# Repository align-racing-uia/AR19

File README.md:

<h1 align="center"> Align Racing 2019 </h1> <br>
<p align="center">
    
</p>

<!-- START doctoc generate TOC please keep comment here to allow auto update -->
<!-- DON'T EDIT THIS SECTION, INSTEAD RE-RUN doctoc TO UPDATE -->
## Table of contents

- [Introduction](#introduction)
- [Align Racing UiA](#alignracinguia)
- [Rules for file structure](#rulesforfilestructure)
- [License](#license)

<!-- END doctoc generated TOC please keep comment here to allow auto update -->

## Introduction

This is the repository for Align Racing's 2019 formula student race car.

## Align Racing UiA

<a href="http://www.alignracing.no/">Align Racing UiA (AR)</a> is a multidisciplinary student organisation at <a href="https://www.uia.no/">The University of Agder (UiA)</a>, that take part in the world’s largest yearly engineering competition; <a href="https://www.imeche.org/events/formula-student">Formula Student (FS)</a>. The organisation continuously consists of around 60 students, from a wide variety of disciplines. The competition includes developing, building, budgeting and marketing a small scale formula type racing car. AR takes this a bit further by having more focus on developing a strong organisation, open for all disciplines, that gives the members a taste of future work-life.

## Rules for directory structure
<h4>General directory structure:</h4>

* AR”YEAR”
    * AR”YEAR”_“PROJECT”
        - AR”YEAR”_“PROJECT”
            - “PROJECT”_code
            - “PROJECT”_datasheets
            - “PROJECT”_images
            - “PROJECT”_schematic
            - “PROJECT”_simulink

<h4>Directory structure example:</h4>

* AR19
    * AR19_ETC
        - AR19_ETC_ACM_ETB
            - ACM_ETB_code
            - ACM_ETB_datasheets
            - ACM_ETB_images
            - ACM_ETB_schematic
            - ACM_ETB_simulink

## License
All content included in this Git repository is under the license:

Creative Commons Attribution-NonCommercial-ShareAlike 4.0 International

You are free to:
* <b> Share </b> — copy and redistribute the material in any medium or format
* <b> Adapt </b> — remix, transform, and build upon the material

Under the following terms:
* <b> Attribution </b> — You must give appropriate credit, provide a link to the license, and indicate if changes were made. You may do so in any reasonable manner, but not in any way that suggests the licensor endorses you or your use.
* <b> NonCommercial </b> — You may not use the material for commercial purposes.
* <b> ShareAlike </b> — If you remix, transform, or build upon the material, you must distribute your contributions under the same license as the original.
* <b> No additional restrictions </b> — You may not apply legal terms or technological measures that legally restrict others from doing anything the license permits.

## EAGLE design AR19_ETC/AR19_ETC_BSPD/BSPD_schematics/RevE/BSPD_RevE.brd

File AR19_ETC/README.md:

<h1 align="center"> Align Racing 2019 Electronic Throttle Control </h1> <br>
<p align="center">
    
</p>

<!-- START doctoc generate TOC please keep comment here to allow auto update -->
<!-- DON'T EDIT THIS SECTION, INSTEAD RE-RUN doctoc TO UPDATE -->
## Table of contents

- [Introduction](#introduction)
- [Align Racing UiA](#alignracinguia)
- [Contributors](#contributors)
- [Acknowledgments](#acknowledgments)
- [License](#license)

<!-- END doctoc generated TOC please keep comment here to allow auto update -->

## Introduction

This is the directory for Align Racing 2019 Electronic Throttle Control bachelor thesis. The goal of the project is to develop and implement an electronic throttle control system for a Formula Student race car.

## Align Racing UiA

<a href="http://www.alignracing.no/">Align Racing UiA (AR)</a> is a multidisciplinary student organisation at <a href="https://www.uia.no/">The University of Agder (UiA)</a>, that take part in the world’s largest yearly engineering competition; <a href="https://www.imeche.org/events/formula-student">Formula Student (FS)</a>. The organisation continuously consists of around 60 students, from a wide variety of disciplines. The competition includes developing, building, budgeting and marketing a small scale formula type racing car. AR takes this a bit further by having more focus on developing a strong organisation, open for all disciplines, that gives the members a taste of future work-life.

## Contributors

<div align="center">

</div>

<div align="center">

</div>

## Acknowledgments

Special thanks to our supervisor <a href="https://www.uia.no/kk/profil/kristimk">Kristian Muri Knausgård</a> for helping and supporting our project.

## License
All content included in this Git repository is under the license:

Creative Commons Attribution-NonCommercial-ShareAlike 4.0 International

You are free to:
* <b> Share </b> — copy and redistribute the material in any medium or format
* <b> Adapt </b> — remix, transform, and build upon the material

Under the following terms:
* <b> Attribution </b> — You must give appropriate credit, provide a link to the license, and indicate if changes were made. You may do so in any reasonable manner, but not in any way that suggests the licensor endorses you or your use.
* <b> NonCommercial </b> — You may not use the material for commercial purposes.
* <b> ShareAlike </b> — If you remix, transform, or build upon the material, you must distribute your contributions under the same license as the original.
* <b> No additional restrictions </b> — You may not apply legal terms or technological measures that legally restrict others from doing anything the license permits.

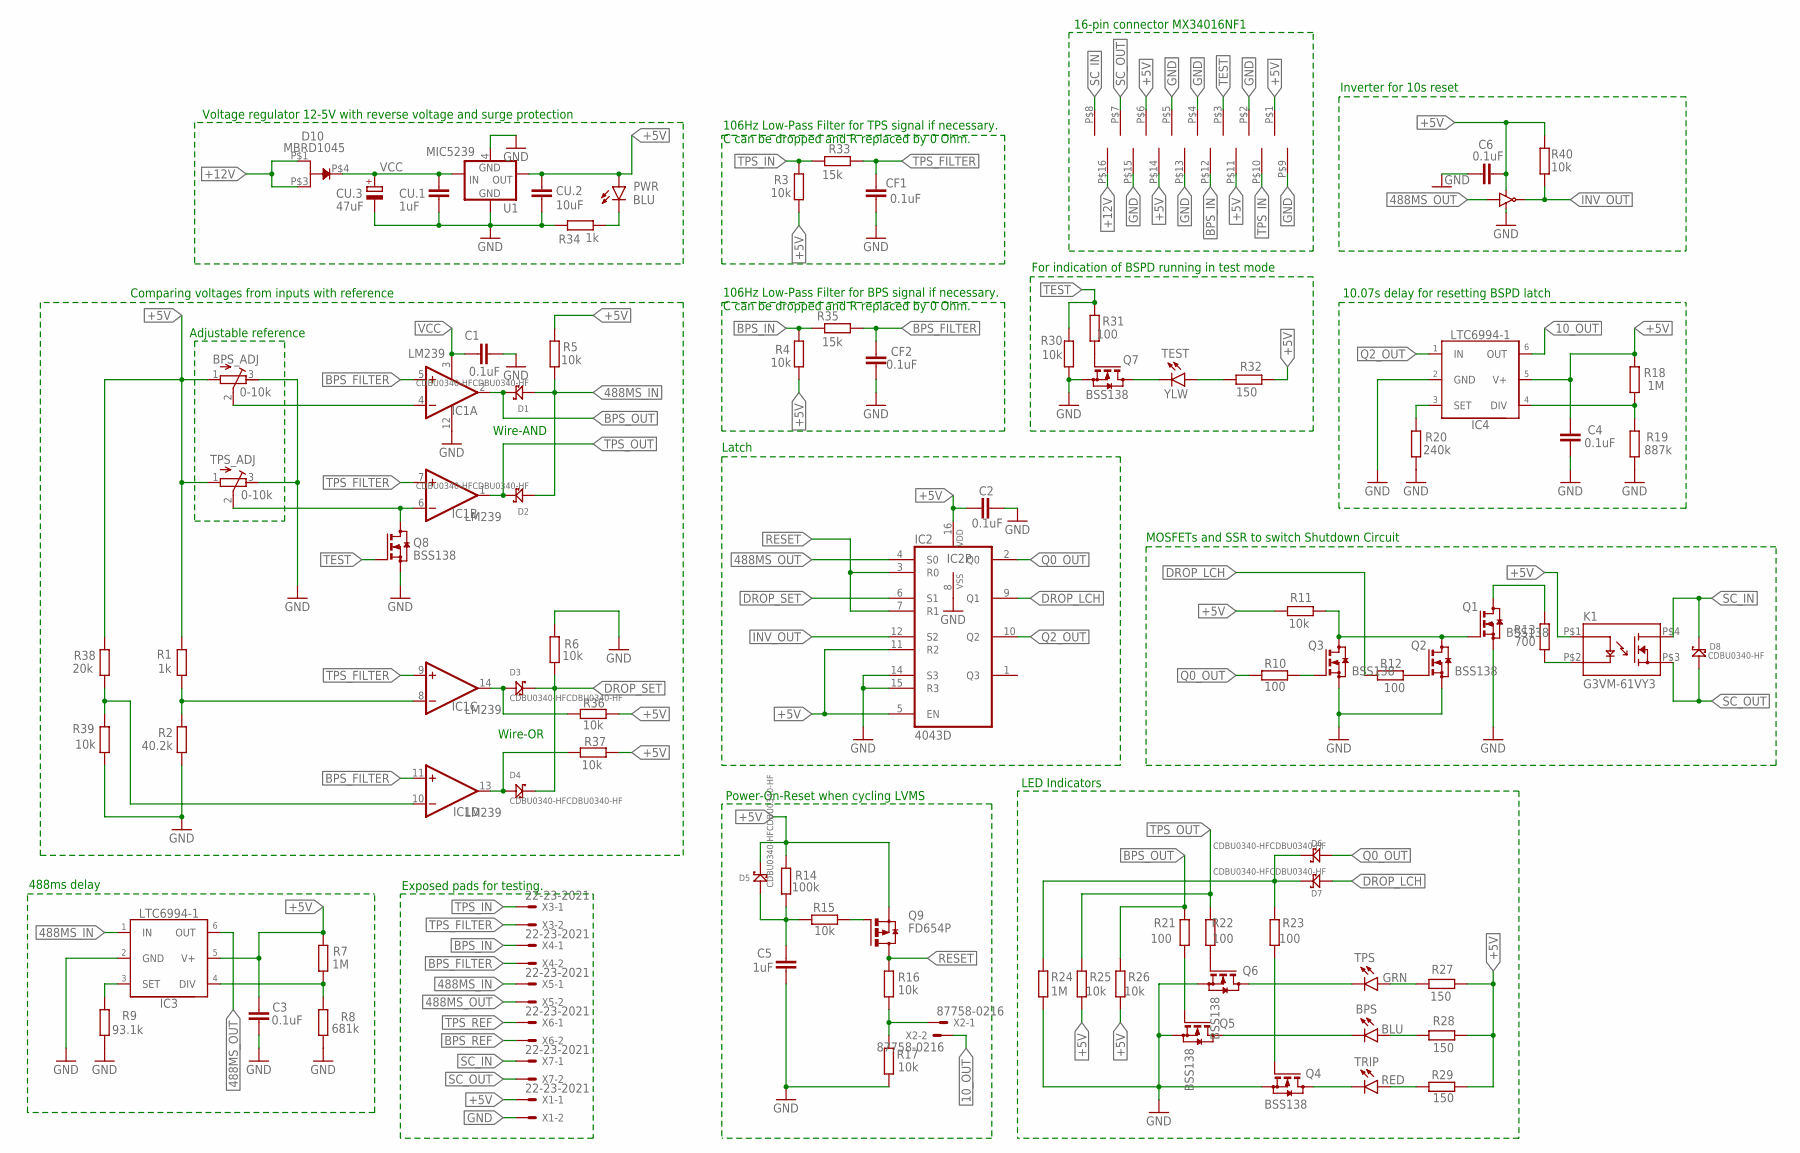
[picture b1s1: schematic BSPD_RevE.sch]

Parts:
BPS: BLU; SML1206
BPS_ADJ: 0-10k; RTRIM3296W
C1, C2, C3, C4, C6: 0.1uF; C0603
C5: 1uF; C0603
CF1, CF2: 0.1uF; C0603
CU.1: 1uF; C0603
CU.2: 10uF; C0603
CU.3: 47uF; E2-5
D1, D2, D3, D4, D5, D6, D7: CDBU0340-HFCDBU0340-HF; DIOM1709X85
D8: CDBU0340-HF; DIOM1709X85
D10: MBRD1045; DPAK
IC1: LM239; SO14
IC2: 4043D; SO16
IC3, IC4: LTC6994-1; TSOT23-6
K1: G3VM-61VY3; SOP-4
P1: MX34016NF1
PWR: BLU; SML1206
Q1, Q2, Q3, Q4, Q5, Q6, Q7, Q8: BSS138; SOT23
Q9: FD654P; SOT-23-6
R1, R34: 1k; R0603
R2: 40.2k; R0603
R3, R4, R5, R6, R11, R15, R16, R17, R25, R26, R30, R36, R37, R39, R40: 10k; R0603
R7, R18, R24: 1M; R0603
R8: 681k; R0603
R9: 93.1k; R0603
R10, R12, R21, R22, R23, R31: 100; R0603
R13: 700; R0603
R14: 100k; R0603
R19: 887k; R0603
R20: 240k; R0603
R27, R28, R29, R32: 150; R0603
R33, R35: 15k; R0603
R38: 20k; R0603
TEST: YLW; SML1206
TPS: GRN; SML1206
TPS_ADJ: 0-10k; RTRIM3296W
TRIP: RED; SML1206
U1: MIC5239; SOT223
U2: 74LVC1G06; SOT353-1
X1, X3, X4, X5, X6, X7: 22-23-2021
X2: 87758-0216

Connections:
10_OUT: IC4.6 (OUT), X2.2
488MS_IN: D1.2$A (A), D2.2$A (A), IC3.1 (IN), R5.1, X5.1
488MS_OUT: IC2.4 (S0), IC3.6 (OUT), U2.P$2 (A), X5.2
+5V: BPS_ADJ.1 (A), C2.1, C3.2, C4.2, C6.2, CU.2.1, D5.1$K (K), IC2.5 (EN), IC2.11 (R2), IC2.16 (VDD), IC3.5 (V+), IC4.5 (V+), K1.P$1 (2), P1.P$1, P1.P$6, P1.P$11, P1.P$14, PWR.A, Q9.4 (S), R1.2, R3.1, R4.1, R5.2, R7.2, R11.2, R14.2, R18.2, R25.1, R26.1, R27.2, R28.2, R29.2, R32.2, R36.1, R37.1, R38.2, R40.2, TPS_ADJ.1 (A), U1.3 (OUT), U2.P$5 (VCC), X1.1
+12V: D10.P$1, D10.P$3, P1.P$16
BPS_DROP: D4.2$A (A), IC1.13 (OUT), R37.2
BPS_FILTER: CF2.2, IC1.5 (+IN), IC1.11 (+IN), R35.1, X4.2
BPS_IN: P1.P$12, R4.2, R35.2, X4.1
BPS_OUT: D1.1$K (K), IC1.2 (OUT), R21.2, R26.2
BPS_REF: BPS_ADJ.2 (S), IC1.4 (-IN), X6.2
DROP_LCH: D7.2$A (A), IC2.9 (Q1), R12.2
DROP_SET: D3.1$K (K), D4.1$K (K), IC2.6 (S1), R6.1
GND: BPS_ADJ.3 (E), C1.2, C2.2, C3.1, C4.1, C5.1, C6.1, CF1.1, CF2.1, CU.1.2, CU.2.2, CU.3.-, IC1.12 (V-), IC2.8 (VSS), IC2.14 (S3), IC2.15 (R3), IC3.2 (GND), IC4.2 (GND), P1.P$2, P1.P$4, P1.P$5, P1.P$9, P1.P$13, P1.P$15, Q1.2 (S), Q2.2 (S), Q3.2 (S), Q4.2 (S), Q5.2 (S), Q6.2 (S), Q7.2 (S), Q8.2 (S), R2.1, R6.2, R8.1, R9.1, R17.2, R19.1, R20.1, R24.1, R30.1, R34.1, R39.1, TPS_ADJ.3 (E), U1.2 (GND), U1.4 (GND_TAB), U2.P$3 (GND), X1.2
INV_OUT: IC2.12 (S2), R40.1, U2.P$4 (Y)
LED_DROP: Q7.3 (D), TEST.C
unnamed: R16.2, R17.1, X2.1
unnamed: Q1.3 (D), R13.2
unnamed: IC1.8 (-IN), R1.1, R2.2
unnamed: IC3.4 (DIV), R7.1, R8.2
unnamed: Q1.1 (G), Q2.3 (D), Q3.3 (D), R11.1
unnamed: R27.1, TPS.A
unnamed: BPS.A, R28.1
unnamed: BPS.C, Q5.3 (D)
unnamed: Q6.3 (D), TPS.C
unnamed: R29.1, TRIP.A
unnamed: Q4.3 (D), TRIP.C
unnamed: Q2.1 (G), R12.1
unnamed: C5.2, D5.2$A (A), R14.1, R15.2
unnamed: PWR.C, R34.2
unnamed: K1.P$2 (1), R13.1
unnamed: Q5.1 (G), R21.1
unnamed: Q6.1 (G), R22.1
unnamed: Q4.1 (G), R23.1
unnamed: R32.1, TEST.A
unnamed: IC4.4 (DIV), R18.1, R19.2
unnamed: IC4.3 (SET), R20.2
unnamed: Q3.1 (G), R10.2
unnamed: Q7.1 (G), R31.1
unnamed: IC3.3 (SET), R9.2
unnamed: D6.1$K (K), D7.1$K (K), R23.2, R24.2
unnamed: Q9.3 (G), R15.1
unnamed: IC1.10 (-IN), R38.1, R39.2
Q0_OUT: D6.2$A (A), IC2.2 (Q0), R10.1
Q2_OUT: IC2.10 (Q2), IC4.1 (IN)
RESET: IC2.3 (R0), IC2.7 (R1), Q9.1 (D), Q9.2 (D), Q9.5 (D), Q9.6 (D), R16.1
SC_IN: D8.1$K (K), K1.P$4 (4), P1.P$8, X7.1
SC_OUT: D8.2$A (A), K1.P$3 (3), P1.P$7, X7.2
TEST: P1.P$3, Q8.1 (G), R30.2, R31.2
TPS_DROP: D3.2$A (A), IC1.14 (OUT), R36.2
TPS_FILTER: CF1.2, IC1.7 (+IN), IC1.9 (+IN), R33.1, X3.2
TPS_IN: P1.P$10, R3.2, R33.2, X3.1
TPS_OUT: D2.1$K (K), IC1.1 (OUT), R22.2, R25.2
TPS_REF: IC1.6 (-IN), Q8.3 (D), TPS_ADJ.2 (S), X6.1
VCC: C1.1, CU.1.1, CU.3.+, D10.P$4, IC1.3 (V+), U1.1 (IN)

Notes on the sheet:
Adjustable reference
LED Indicators
16-pin connector MX34016NF1
Voltage regulator 12-5V with reverse voltage and surge protection
For indication of BSPD running in test mode
10.07s delay for resetting BSPD latch
MOSFETs and SSR to switch Shutdown Circuit
488ms delay
Power-On-Reset when cycling LVMS
Latch
106Hz Low-Pass Filter for TPS signal if necessary. C can be dropped and R replaced by 0 Ohm.
Comparing voltages from inputs with reference
Wire-OR
Wire-AND
106Hz Low-Pass Filter for BPS signal if necessary. C can be dropped and R replaced by 0 Ohm.
Exposed pads for testing.
Inverter for 10s reset

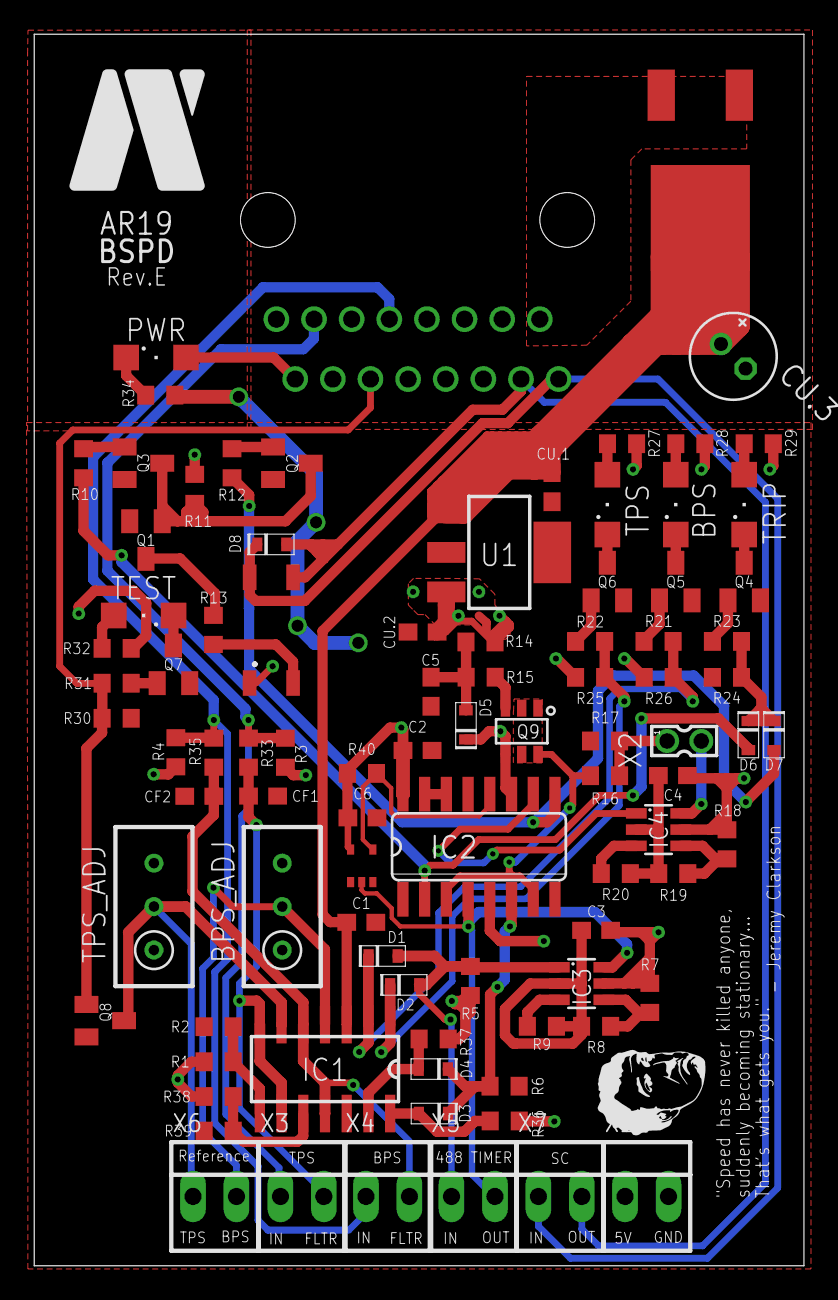
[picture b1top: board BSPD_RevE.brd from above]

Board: 2 copper layers, 45.0 x 72.0 mm, 91 parts (0 on the bottom side), 54 nets.

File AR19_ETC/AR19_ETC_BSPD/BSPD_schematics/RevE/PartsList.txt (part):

Partlist

Exported from BSPD_RevE.sch at 29.05.2019 15:06

EAGLE Version 9.2.0 Copyright (c) 1988-2018 Autodesk, Inc.

Assembly variant: 

Part     Value                  Device                 Package     Library                 Sheet

BPS      BLU                    LEDSML1206             SML1206     led                     1
BPS_ADJ  0-10k                  R-TRIMM3296W           RTRIM3296W  rcl                     1
C1       0.1uF                  C-EUC0603              C0603       rcl                     1
C2       0.1uF                  C-EUC0603              C0603       rcl                     1
C3       0.1uF                  C-EUC0603              C0603       rcl                     1
C4       0.1uF                  C-EUC0603              C0603       rcl                     1
C5       1uF                    C-EUC0603              C0603       rcl                     1
C6       0.1uF                  C-EUC0603              C0603       rcl                     1
CF1      0.1uF                  C-EUC0603              C0603       rcl                     1
CF2      0.1uF                  C-EUC0603              C0603       rcl                     1
CU.1     1uF                    C-EUC0603              C0603       rcl                     1
CU.2     10uF                   C-EUC0603              C0603       rcl                     1
CU.3     47uF                   CPOL-EUE2-5            E2-5        rcl                     1
D1       CDBU0340-HFCDBU0340-HF CDBU0340-HFCDBU0340-HF DIOM1709X85 BSPD                    1
D2       CDBU0340-HFCDBU0340-HF CDBU0340-HFCDBU0340-HF DIOM1709X85 BSPD                    1
D3       CDBU0340-HFCDBU0340-HF CDBU0340-HFCDBU0340-HF DIOM1709X85 BSPD                    1
D4       CDBU0340-HFCDBU0340-HF CDBU0340-HFCDBU0340-HF DIOM1709X85 BSPD                    1
D5       CDBU0340-HFCDBU0340-HF CDBU0340-HFCDBU0340-HF DIOM1709X85 BSPD                    1
D6       CDBU0340-HFCDBU0340-HF CDBU0340-HFCDBU0340-HF DIOM1709X85 BSPD                    1
D7       CDBU0340-HFCDBU0340-HF CDBU0340-HFCDBU0340-HF DIOM1709X85 BSPD                    1
D8       CDBU0340-HF            CDBU0340-HFCDBU0340-HF DIOM1709X85 AR19_ETC                1
D10      MBRD1045               MBRD1045               DPAK        AR19_ETC                1
IC1      LM239                  LM2901D                SO14        linear                  1
IC2      4043D                  4043D                  SO16        40xx                    1
IC3      LTC6994-1              LTC6994-1              TSOT23-6    div1                    1
IC4      LTC6994-1              LTC6994-1              TSOT23-6    div1                    1
K1       G3VM-61VY3             G3VM-61VY3             SOP-4       AR19_ETC                1
P1       MX34016NF1             MX34016NF1             MX34016NF1  AR19_ETC                1
PWR      BLU                    LEDSML1206             SML1206     led                     1
Q1       BSS138                 BSS123                 SOT23       transistor-small-signal 1
Q2       BSS138                 BSS123                 SOT23       transistor-small-signal 1
Q3       BSS138                 BSS123                 SOT23       transistor-small-signal 1
Q4       BSS138                 BSS123                 SOT23       transistor-small-signal 1
Q5       BSS138                 BSS123                 SOT23       transistor-small-signal 1
Q6       BSS138                 BSS123                 SOT23       transistor-small-signal 1
Q7       BSS138                 BSS123                 SOT23       transistor-small-signal 1
Q8       BSS138                 BSS123                 SOT23       transistor-small-signal 1
Q9       FD654P                 FD654P                 SOT-23-6    BSPD                    1
R1       1k                     R-EU_R0603             R0603       rcl                     1
R2       40.2k                  R-EU_R0603             R0603       rcl                     1
R3       10k                    R-EU_R0603             R0603       rcl                     1
R4       10k                    R-EU_R0603             R0603       rcl                     1
R5       10k                    R-EU_R0603             R0603       rcl                     1
R6       10k                    R-EU_R0603             R0603       rcl                     1
R7       1M                     R-EU_R0603             R0603       rcl                     1
R8       681k                   R-EU_R0603             R0603       rcl                     1
R9       93.1k                  R-EU_R0603             R0603       rcl                     1
R10      100                    R-EU_R0603             R0603       rcl                     1
R11      10k                    R-EU_R0603             R0603       rcl                     1
R12      100                    R-EU_R0603             R0603       rcl                     1
R13      700                    R-EU_R0603             R0603       rcl                     1
R14      100k                   R-EU_R0603             R0603       rcl                     1
R15      10k                    R-EU_R0603             R0603       rcl                     1
R16      10k                    R-EU_R0603             R0603       rcl                     1
R17      10k                    R-EU_R0603             R0603       rcl                     1
R18      1M                     R-EU_R0603             R0603       rcl                     1
R19      887k                   R-EU_R0603             R0603       rcl                     1
R20      240k                   R-EU_R0603             R0603       rcl                     1
R21      100                    R-EU_R0603             R0603       rcl                     1
R22      100                    R-EU_R0603             R0603       rcl                     1
R23      100                    R-EU_R0603             R0603       rcl                     1
R24      1M                     R-EU_R0603             R0603       rcl                     1
R25      10k                    R-EU_R0603             R0603       rcl                     1
R26      10k                    R-EU_R0603             R0603       rcl                     1
R27      150                    R-EU_R0603             R0603       rcl                     1
R28      150                    R-EU_R0603             R0603       rcl                     1
R29      150                    R-EU_R0603             R0603       rcl                     1
R30      10k                    R-EU_R0603             R0603       rcl                     1
R31      100                    R-EU_R0603             R0603       rcl                     1
R32      150                    R-EU_R0603             R0603       rcl                     1
R33      15k                    R-EU_R0603             R0603       rcl                     1
R34      1k                     R-EU_R0603             R0603       rcl                     1
R35      15k                    R-EU_R0603             R0603       rcl                     1
R36      10k                    R-EU_R0603             R0603       rcl                     1
R37      10k                    R-EU_R0603             R0603       rcl                     1
R38      20k                    R-EU_R0603             R0603       rcl                     1
R39      10k                    R-EU_R0603             R0603       rcl                     1
R40      10k                    R-EU_R0603             R0603       rcl                     1
TEST     YLW                    LEDSML1206             SML1206     led                     1
TPS      GRN                    LEDSML1206             SML1206     led                     1
TPS_ADJ  0-10k                  R-TRIMM3296W           RTRIM3296W  rcl                     1
TRIP     RED                    LEDSML1206             SML1206     led                     1
U1       MIC5239                MIC5239                SOT223      BSPD                    1
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
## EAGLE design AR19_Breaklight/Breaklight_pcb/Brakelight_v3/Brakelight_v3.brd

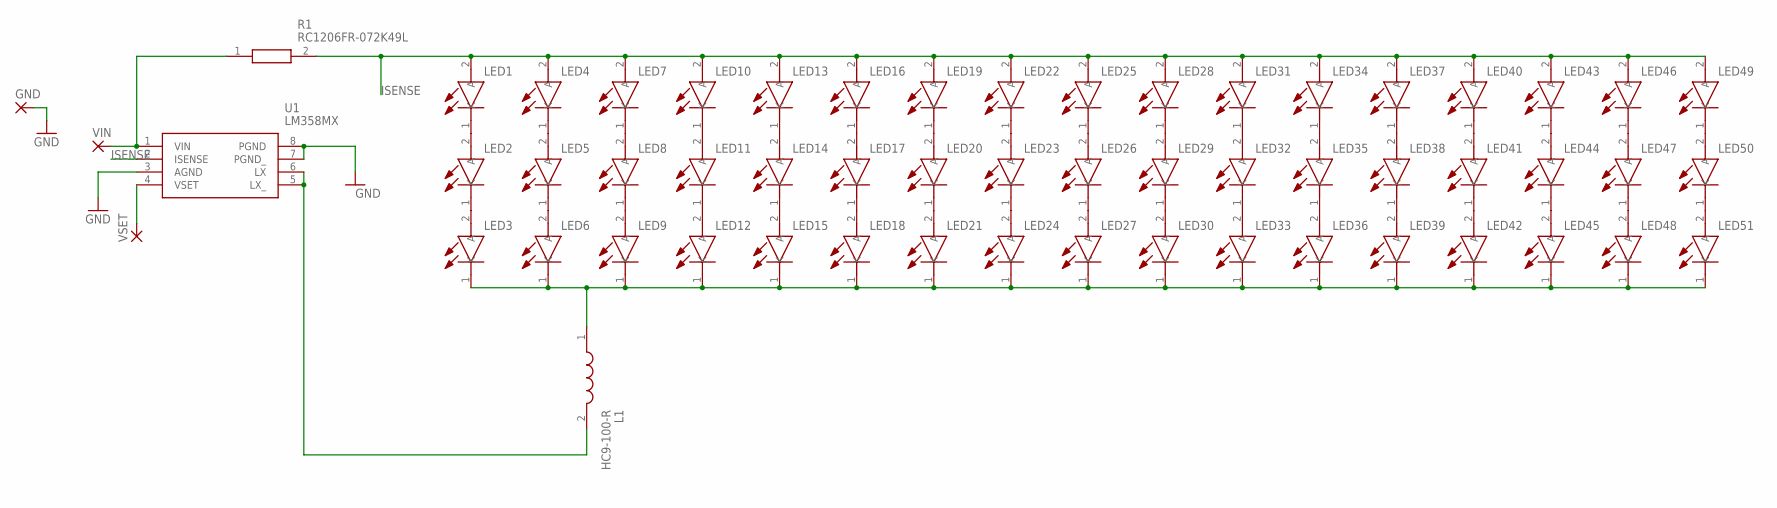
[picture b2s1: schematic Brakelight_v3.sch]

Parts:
GND: 2,54/1,1
L1: HC9-100-R; INDPM141131X770N
LED1, LED2, LED3, LED4, LED5, LED6, LED7, LED8, LED9, LED10, LED11, LED12, LED13, LED14, LED15, LED16, LED17, LED18, LED19, LED20, LED21, LED22, LED23, LED24, LED25, LED26, LED27, LED28, LED29, LED30, LED31, LED32, LED33, LED34, LED35, LED36, LED37, LED38, LED39, LED40, LED41, LED42, LED43, LED44, LED45, LED46, LED47, LED48, LED49, LED50, LED51: SSL-LX5093TC; SSL-LX5093SGC/B
R1: RC1206FR-072K49L; RESC3116X65N
U1: LM358MX; SOP127P600X180-8N
VIN: 2,54/1,1
VSET: 2,54/1,1

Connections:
GND: GND.1, U1.3 (AGND), U1.7 (PGND_), U1.8 (PGND)
ISENSE: LED1.2 (A), LED4.2 (A), LED7.2 (A), LED10.2 (A), LED13.2 (A), LED16.2 (A), LED19.2 (A), LED22.2 (A), LED25.2 (A), LED28.2 (A), LED31.2 (A), LED34.2 (A), LED37.2 (A), LED40.2 (A), LED43.2 (A), LED46.2 (A), LED49.2 (A), R1.2, U1.2 (ISENSE)
LEDK: L1.1, LED3.1 (K), LED6.1 (K), LED9.1 (K), LED12.1 (K), LED15.1 (K), LED18.1 (K), LED21.1 (K), LED24.1 (K), LED27.1 (K), LED30.1 (K), LED33.1 (K), LED36.1 (K), LED39.1 (K), LED42.1 (K), LED45.1 (K), LED48.1 (K), LED51.1 (K)
unnamed: LED1.1 (K), LED2.2 (A)
unnamed: LED2.1 (K), LED3.2 (A)
unnamed: LED4.1 (K), LED5.2 (A)
unnamed: LED5.1 (K), LED6.2 (A)
unnamed: LED7.1 (K), LED8.2 (A)
unnamed: LED8.1 (K), LED9.2 (A)
unnamed: LED10.1 (K), LED11.2 (A)
unnamed: LED11.1 (K), LED12.2 (A)
unnamed: LED13.1 (K), LED14.2 (A)
unnamed: LED14.1 (K), LED15.2 (A)
unnamed: LED16.1 (K), LED17.2 (A)
unnamed: LED17.1 (K), LED18.2 (A)
unnamed: LED19.1 (K), LED20.2 (A)
unnamed: LED20.1 (K), LED21.2 (A)
unnamed: LED22.1 (K), LED23.2 (A)
unnamed: LED23.1 (K), LED24.2 (A)
unnamed: LED25.1 (K), LED26.2 (A)
unnamed: LED26.1 (K), LED27.2 (A)
unnamed: LED28.1 (K), LED29.2 (A)
unnamed: LED29.1 (K), LED30.2 (A)
unnamed: LED31.1 (K), LED32.2 (A)
unnamed: LED32.1 (K), LED33.2 (A)
unnamed: LED34.1 (K), LED35.2 (A)
unnamed: LED35.1 (K), LED36.2 (A)
unnamed: LED37.1 (K), LED38.2 (A)
unnamed: LED38.1 (K), LED39.2 (A)
unnamed: LED40.1 (K), LED41.2 (A)
unnamed: LED41.1 (K), LED42.2 (A)
unnamed: LED43.1 (K), LED44.2 (A)
unnamed: LED44.1 (K), LED45.2 (A)
unnamed: LED46.1 (K), LED47.2 (A)
unnamed: LED47.1 (K), LED48.2 (A)
unnamed: LED49.1 (K), LED50.2 (A)
unnamed: LED50.1 (K), LED51.2 (A)
unnamed: U1.4 (VSET), VSET.1
unnamed: L1.2, U1.5 (LX_), U1.6 (LX)
VIN: R1.1, U1.1 (VIN), VIN.1

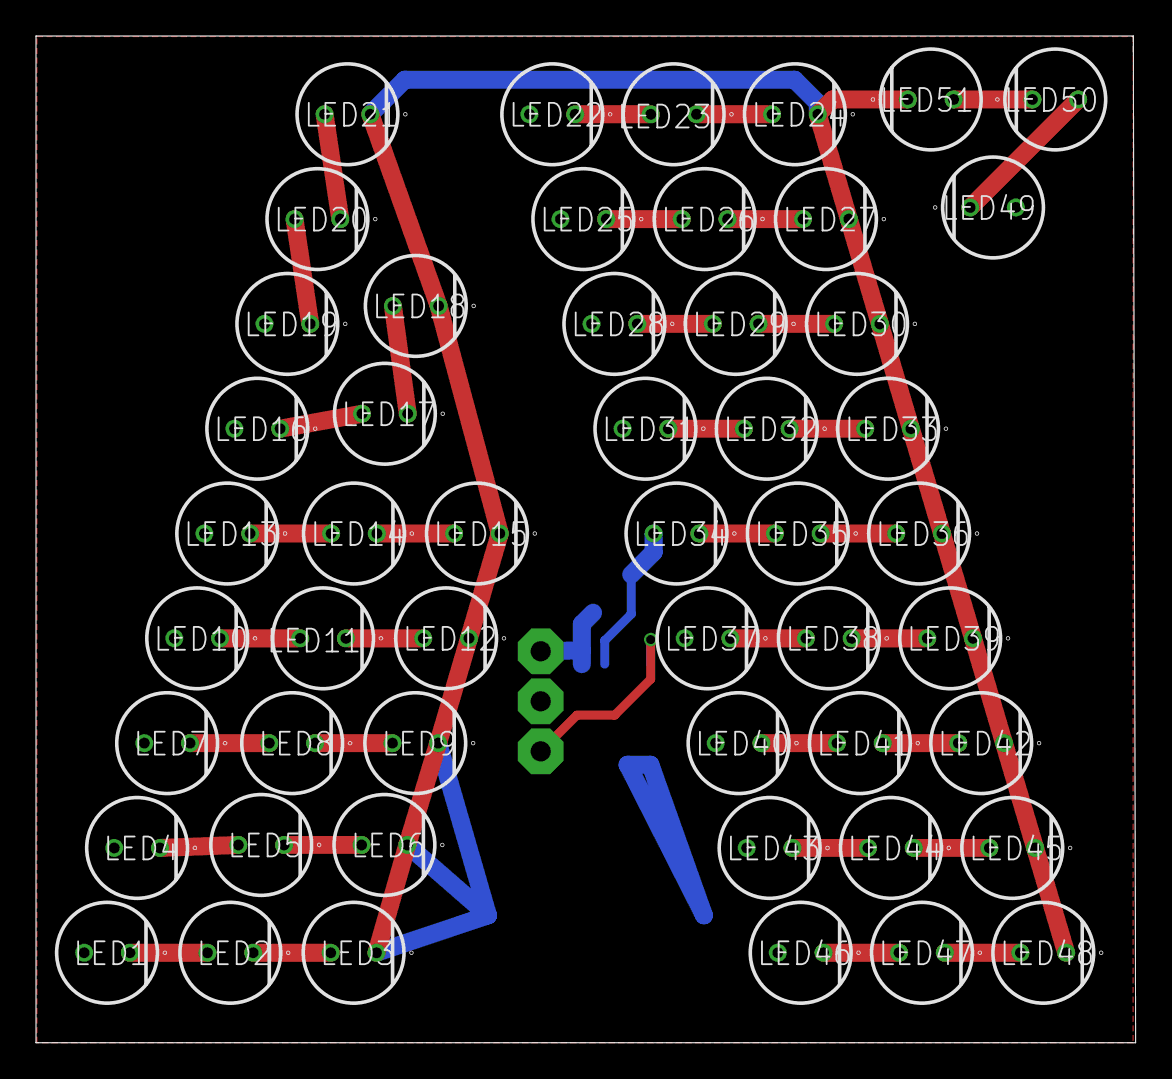
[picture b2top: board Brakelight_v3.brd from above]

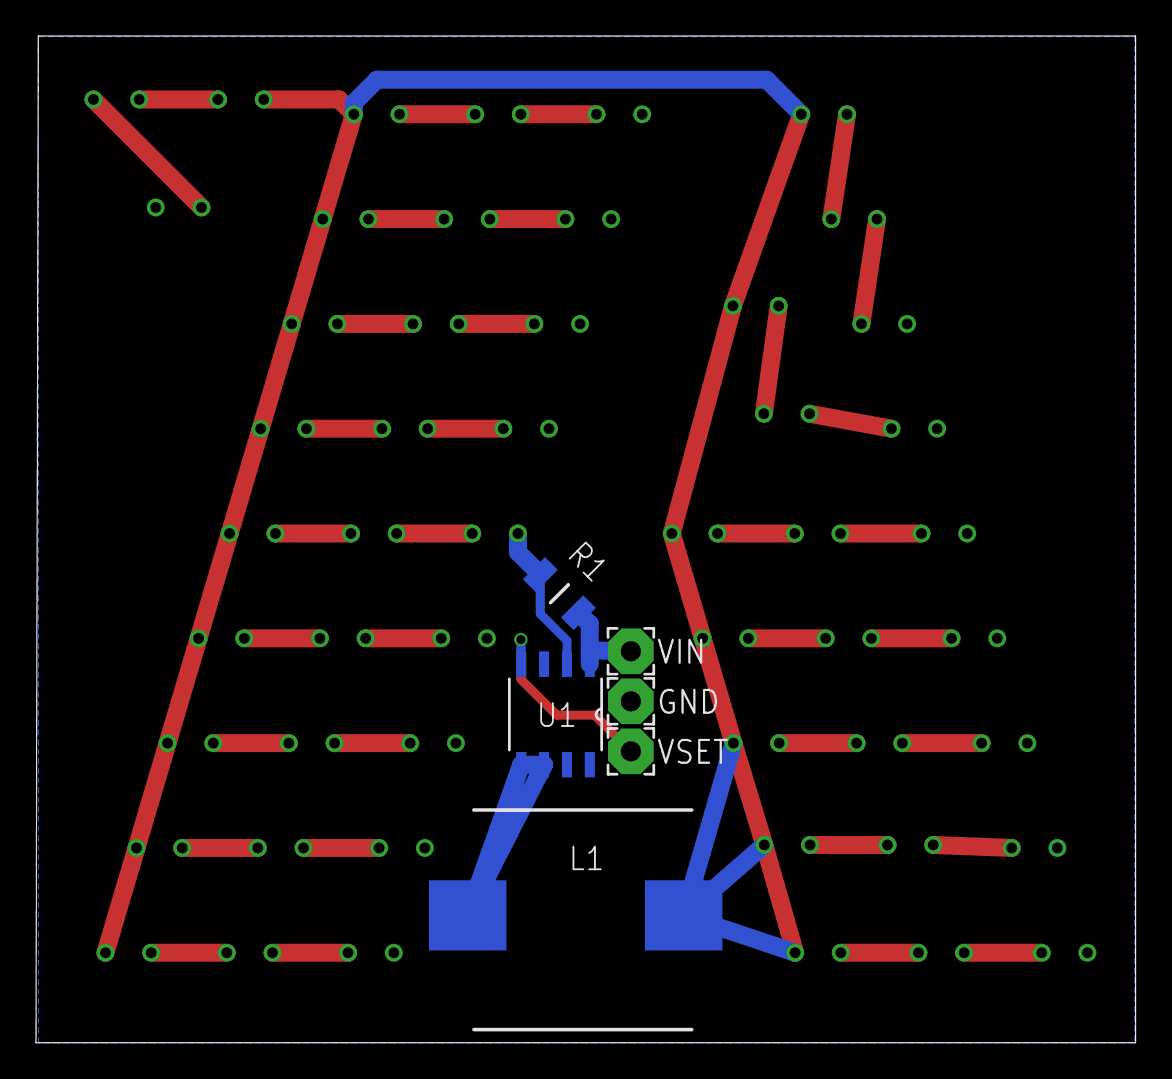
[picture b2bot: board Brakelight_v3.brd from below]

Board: 2 copper layers, 61.1 x 55.9 mm, 57 parts (6 on the bottom side), 40 nets.

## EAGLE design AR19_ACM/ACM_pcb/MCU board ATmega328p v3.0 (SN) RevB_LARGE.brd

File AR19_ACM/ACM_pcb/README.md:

## Align CANbus Module PCB Repository

Created by: snenyl   
Creation date: 26.04.2019 20:38

# Changelog:

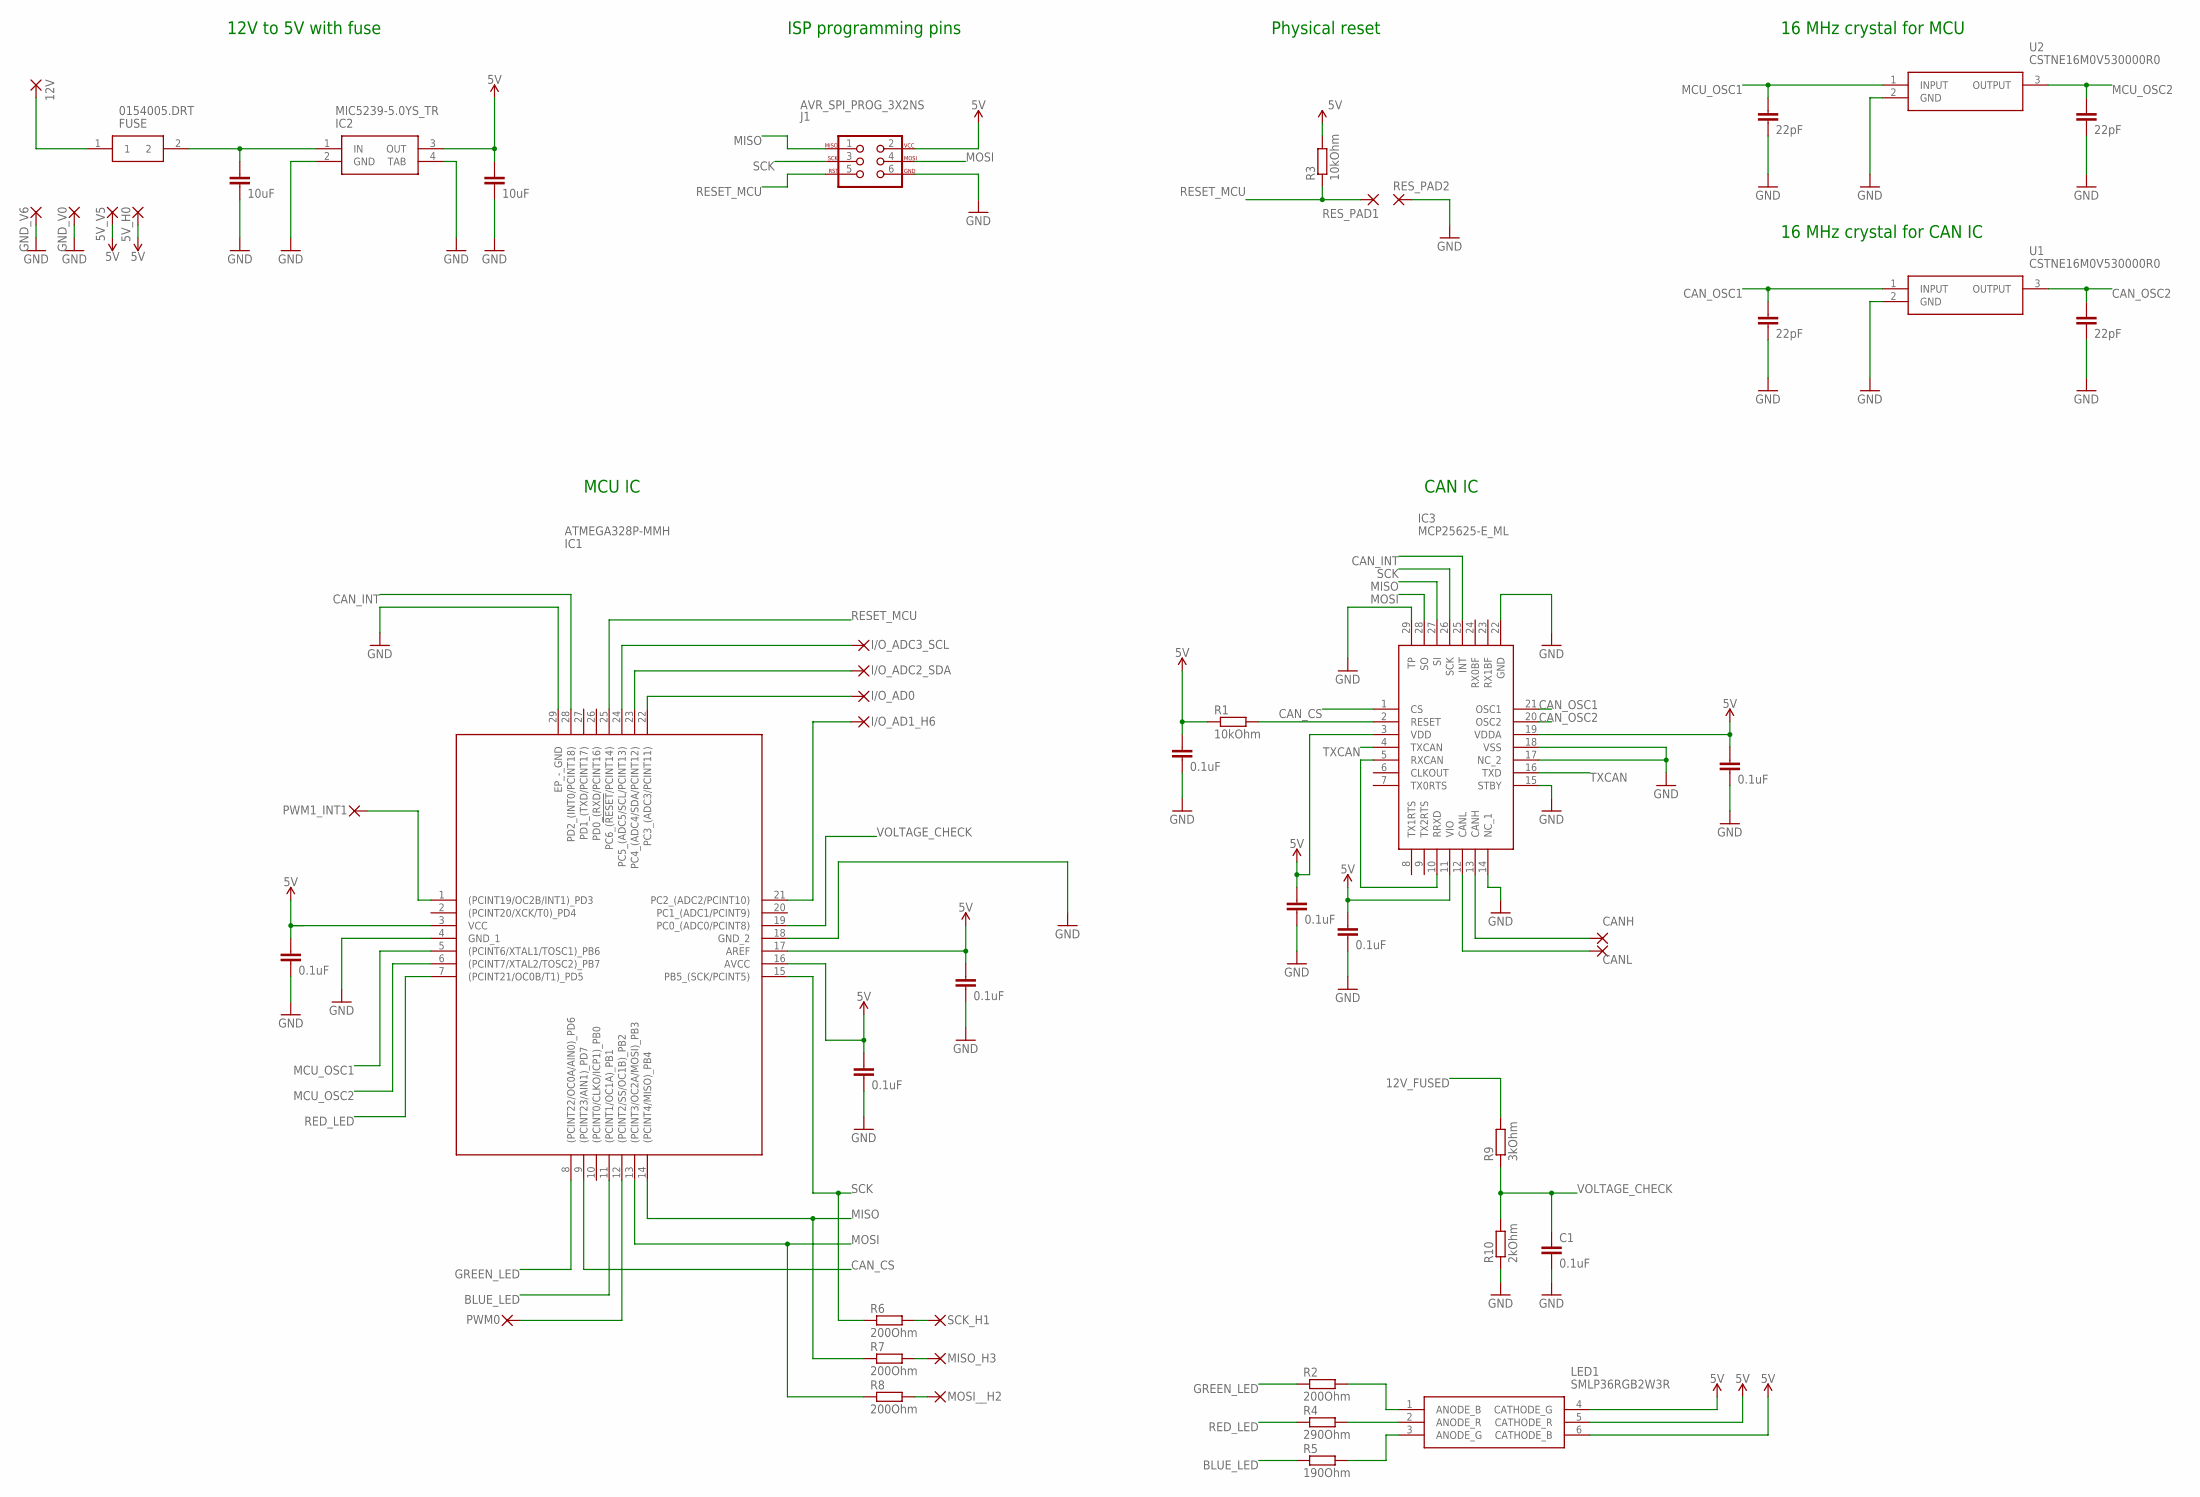
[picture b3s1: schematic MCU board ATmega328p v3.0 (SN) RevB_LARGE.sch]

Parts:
5V: 5V_V5; 2,15/1,0
5V1: 5V_H0; 2,15/1,0
12V: 12V_V7; 2,15/1,0
C1, C6, C7, C8, C12, C13, C16, C17: 0.1uF; C0603
C2, C3, C5, C9: 22pF; C0603
C10, C11: 10uF; C0603
CANH: I/O_CANH_V3; 2,15/1,0
CANL: I/O_CANH_V4; 2,15/1,0
FUSE: 0154005.DRT; 0154001.DRT
GND: GND_V6; 2,15/1,0
GND30: GND_V0; 2,15/1,0
I/O_AD0: I/O_AD0_H7; 2,15/1,0
I/O_AD1: I/O_AD1_H6; 2,15/1,0
I/O_ADC2_SDA: I/O_ADC2_SDA_H5; 2,15/1,0
I/O_ADC3_SCL: I/O_ADC3_SCL_H4; 2,15/1,0
IC1: ATMEGA328P-MMH; QFN45P400X400X100-29N
IC2: MIC5239-5.0YS_TR; SOT230P700X170-4N
IC3: MCP25625-E_ML; QFN65P600X600X100-29N
J1: AVR_SPI_PROG_3X2NS; 2X3-NS
LED1: SMLP36RGB2W3R; ROHM-1510-(0604)
MISO: MISO_H3; 2,15/1,0
MOSI: MOSI__H2; 2,15/1,0
PWM0: PWM0_V2; 2,15/1,0
PWM1_INT1: PWM0_INT_V1; 2,15/1,0
R1, R3: 10kOhm; R0603
R2, R6, R7, R8: 200Ohm; R0603
R4: 290Ohm; R0603
R5: 190Ohm; R0603
R9: 3kOhm; R0603
R10: 2kOhm; R0603
RES_PAD1: RES_PAD; SMD1,27-2,54
RES_PAD2: RES_PAD2; SMD1,27-2,54
SCK: SCK_H1; 2,15/1,0
U1, U2: CSTNE16M0V530000R0

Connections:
5V: 5V.1, 5V1.1, C6.1, C7.1, C8.1, C11.1, C12.1, C13.1, C16.1, C17.1, IC1.3 (VCC), IC1.16 (AVCC), IC1.17 (AREF), IC2.3 (OUT), IC3.3 (VDD), IC3.11 (VIO), IC3.19 (VDDA), J1.2, LED1.4 (CATHODE_G), LED1.5 (CATHODE_R), LED1.6 (CATHODE_B), R1.1, R3.2
12V_FUSED: C10.1, FUSE.2, IC2.1 (IN), R9.2
12V_UNFUSED: 12V.1, FUSE.1
BLUE_LED: IC1.11 ((PCINT1/OC1A)_PB1), R5.1
CANH: CANH.1, IC3.13 (CANH)
CANL: CANL.1, IC3.12 (CANL)
CAN_CS: IC1.9 ((PCINT23/AIN1)_PD7), IC3.1 (CS)
CAN_INT: IC1.28 (PD2_(INT0/PCINT18)), IC3.25 (INT)
CAN_OSC1: C5.1, IC3.21 (OSC1), U1.1 (INPUT)
CAN_OSC2: C2.1, IC3.20 (OSC2), U1.3 (OUTPUT)
GND: C1.2, C2.2, C3.2, C5.2, C6.2, C7.2, C8.2, C9.2, C10.2, C11.2, C12.2, C13.2, C16.2, C17.2, GND.1, GND30.1, IC1.4 (GND_1), IC1.18 (GND_2), IC1.29 (EP_-_GND), IC2.2 (GND), IC2.4 (TAB), IC3.14 (NC_1), IC3.15 (STBY), IC3.17 (NC_2), IC3.18 (VSS), IC3.22 (GND), IC3.29 (TP), J1.6, R10.1, RES_PAD2.1, U1.2 (GND), U2.2 (GND)
GREEN_LED: IC1.8 ((PCINT22/OC0A/AIN0)_PD6), R2.1
I/OAD0: I/O_AD0.1, IC1.22 (PC3_(ADC3/PCINT11))
I/OADC2: I/O_ADC2_SDA.1, IC1.23 (PC4_(ADC4/SDA/PCINT12))
I/O_ADC3: I/O_ADC3_SCL.1, IC1.24 (PC5_(ADC5/SCL/PCINT13))
I/O_D2_INT: IC1.1 ((PCINT19/OC2B/INT1)_PD3), PWM1_INT1.1
MCU_OSC1: C3.1, IC1.5 ((PCINT6/XTAL1/TOSC1)_PB6), U2.1 (INPUT)
MCU_OSC2: C9.1, IC1.6 ((PCINT7/XTAL2/TOSC2)_PB7), U2.3 (OUTPUT)
MISO: IC1.14 ((PCINT4/MISO)_PB4), IC3.27 (SI), J1.1, R7.1
MOSI: IC1.13 ((PCINT3/OC2A/MOSI)_PB3), IC3.28 (SO), J1.4, R8.1
unnamed: IC3.2 (RESET), R1.2
unnamed: IC1.12 ((PCINT2/SS/OC1B)_PB2), PWM0.1
unnamed: I/O_AD1.1, IC1.21 (PC2_(ADC2/PCINT10))
unnamed: LED1.1 (ANODE_B), R2.2
unnamed: LED1.2 (ANODE_R), R4.2
unnamed: LED1.3 (ANODE_G), R5.2
unnamed: R6.2, SCK.1
unnamed: MISO.1, R7.2
unnamed: MOSI.1, R8.2
RED_LED: IC1.7 ((PCINT21/OC0B/T1)_PD5), R4.1
RESET_MCU: IC1.25 (PC6_(!RESET!/PCINT14)), J1.5, R3.1, RES_PAD1.1
RXCAN: IC3.5 (RXCAN), IC3.10 (RRXD)
SCK: IC1.15 (PB5_(SCK/PCINT5)), IC3.26 (SCK), J1.3, R6.1
TXCAN: IC3.4 (TXCAN), IC3.16 (TXD)
VOLTAGE_CHECK: C1.1, IC1.19 (PC0_(ADC0/PCINT8)), R9.1, R10.2

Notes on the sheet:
12V to 5V with fuse
ISP programming pins
Physical reset
16 MHz crystal for MCU
16 MHz crystal for CAN IC
CAN IC
MCU IC

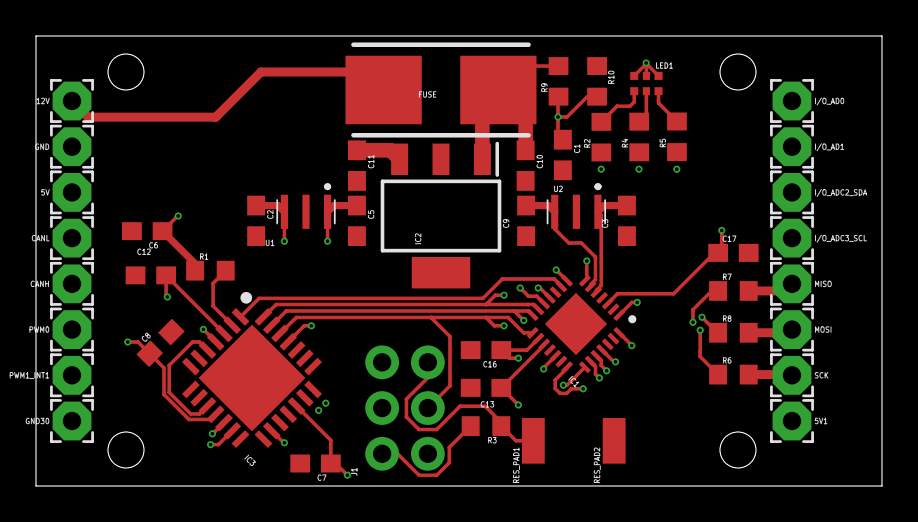
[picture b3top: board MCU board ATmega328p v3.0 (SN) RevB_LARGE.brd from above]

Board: 4 copper layers, 47.0 x 25.0 mm, 50 parts (0 on the bottom side), 35 nets.

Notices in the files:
parts and their libraries:
SparkFun-Connectors: Licensing: Creative Commons ShareAlike 4.0 International - https://creativecommons.org/licenses/by-sa/4.0
